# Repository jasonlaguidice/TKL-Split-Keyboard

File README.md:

# TKL-Split-Keyboard

Forked from Djinn keyboard

Board edge fillet plugin used:
https://github.com/tywtyw2002/FilletEdge

To-do list:
1. Change USB-C connector footprints to hand-solderable version (update BOM part as well)

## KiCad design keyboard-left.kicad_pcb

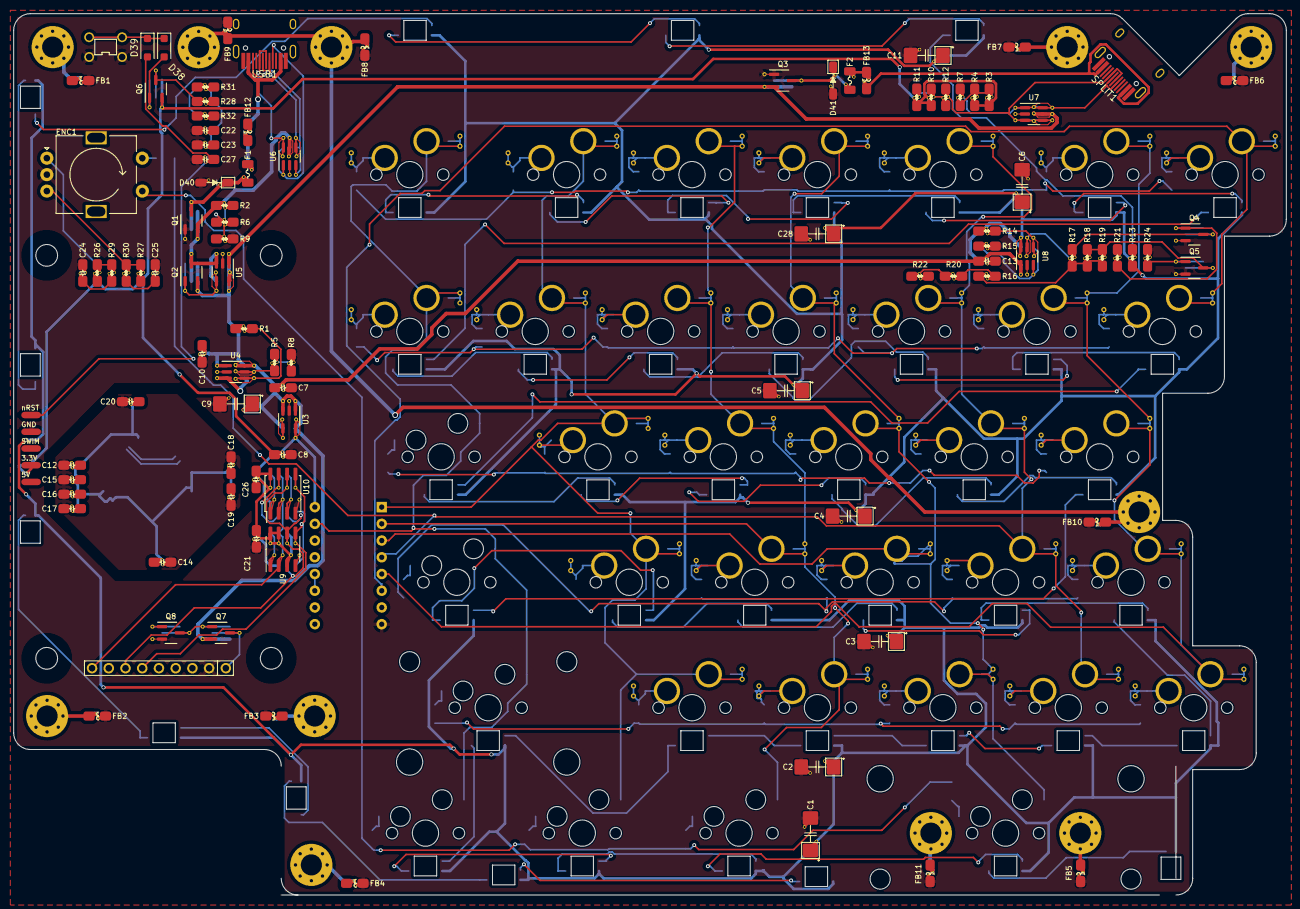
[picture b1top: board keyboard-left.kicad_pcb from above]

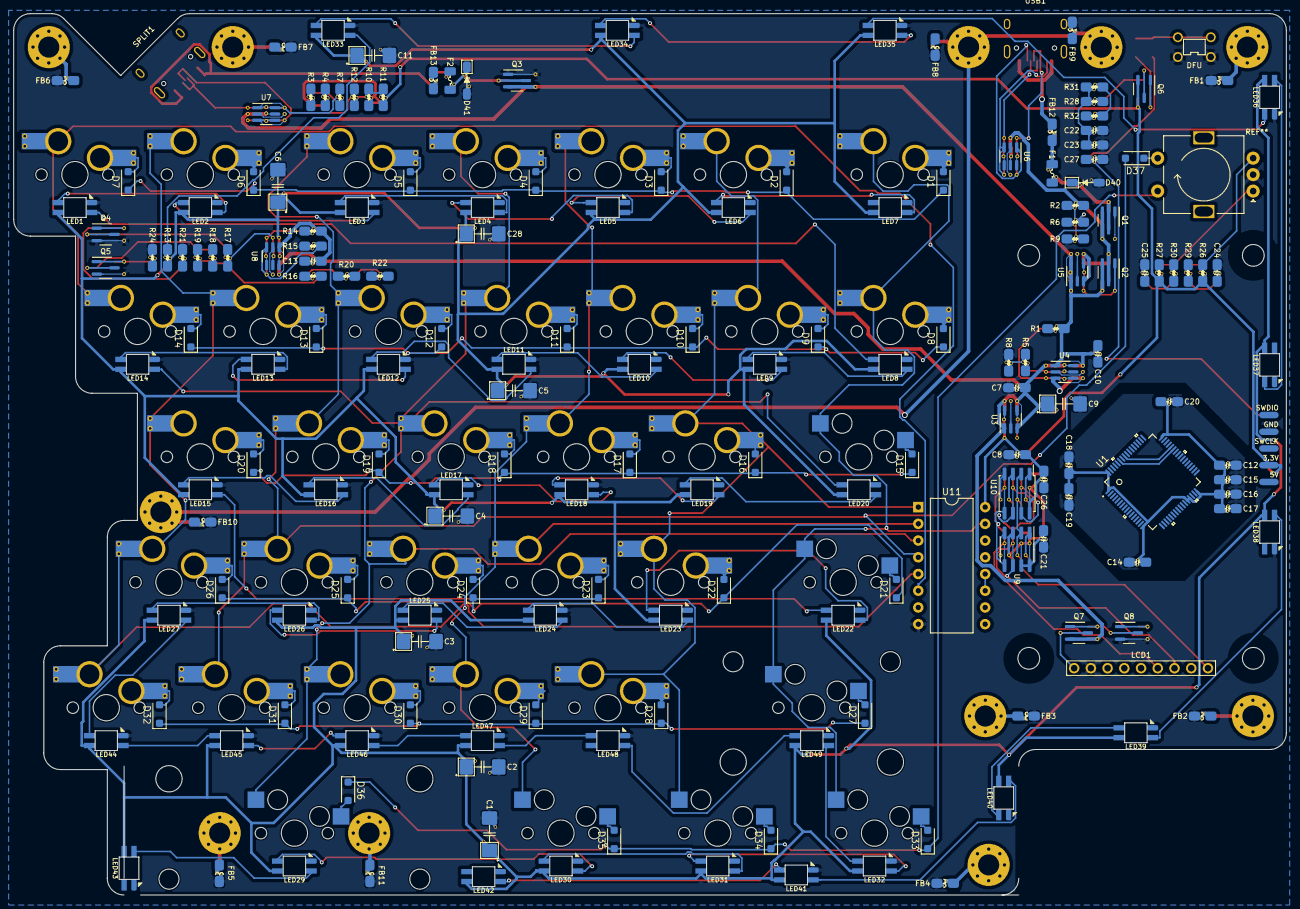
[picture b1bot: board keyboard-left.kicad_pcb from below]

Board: 2 copper layers, 193.3 x 133.9 mm, 232 parts (92 on the bottom side), 169 nets.

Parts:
C1, C2, C3, C4, C5, C6, C9, C11, C28: 100u; CP_6032
C7, C8, C10, C12: 4.7u; C-0805_2012Metric
C13, C14, C15, C16, C17, C18, C19, C20, C21, C22, C23, C24, C25, C26, C27: 100n; C-0805_2012Metric
D1, D2, D3, D4, D5, D6, D7, D8, D9, D10, D11, D12, D13, D14, D15, D16, D17, D18, D19, D20, D21, D22, D23, D24, D25, D26, D27, D28, D29, D30, D31, D32, D33, D34, D35, D36, D37, D38, D39: 1N4148; D_SOD-123F
D40, D41: SMF5.0CA; D_SOD-123
DRILL1, DRILL2, DRILL3, DRILL4, DRILL5, DRILL6, DRILL7, DRILL8, DRILL9, DRILL10, DRILL11: Drill Mountpoint; MountingHole_3.2mm_M3_Pad_Via
ENC1: Rotary_Encoder_Switch; EC11_Switch
F1: 3.0A 1206 Polyfuse; Fuse_1206_3216Metric
F2: 1.5A 1206 Polyfuse; Fuse_1206_3216Metric
FB1, FB2, FB3, FB4, FB5, FB6, FB7, FB8, FB9, FB10, FB11, FB12, FB13: 4A/0805; L-0805_2012Metric
J1: ST-Link Clone (Optional); STLink_SideSocket
LCD1: LCD-ILI9341-2.2in
LED1, LED2, LED3, LED4, LED5, LED6, LED7, LED8, LED9, LED10, LED11, LED12, LED13, LED14, LED15, LED16, LED17, LED18, LED19, LED20, LED22, LED23, LED24, LED25, LED26, LED27, LED29, LED30, LED31, LED32, LED33, LED34, LED35, LED36, LED37, LED38, LED39, LED40, LED41, LED42, LED43, LED44, LED45, LED46, LED47, LED48, LED49: SK6812 Mini-E; SK6812-MINI-E
Q1, Q2, Q3, Q7: AO3401A; SOT-23-3
Q4, Q5: 2N7002; SOT-23-3
Q6: MMUN2133LT1G; SOT-23-3
Q8: MMUN2233LT1G; SOT-23-3
R1, R3, R4, R5, R8, R10, R11, R13, R14, R15, R21, R24, R26, R27, R29, R30: 9.1k; R-0805_2012Metric
R2, R6, R9, R16, R17, R18, R19, R20, R22, R31, R32: 68k; R-0805_2012Metric
R7, R12, R28: 120; R-0805_2012Metric
RESET1: DFU; PushButton_4.5mm
SPLIT1: USB-C-2.0; HRO-TYPE-C-31-M-12-HandSoldering
SW1, SW2, SW3, SW4, SW5, SW6, SW7, SW8, SW9, SW10, SW11, SW12, SW13, SW14, SW16, SW17, SW18, SW19, SW20, SW22, SW23, SW24, SW25, SW26, SW28, SW29, SW30, SW31, SW32: SW_Push; MXOnly-1U-Hotswap-Antishear
SW15: SW_Push; MXOnly-1.5U-Hotswap
SW21: SW_Push; MXOnly-1.75U-Hotswap
SW27: SW_Push; MXOnly-2.25U-Hotswap
SW33, SW34, SW35: SW_Push; MXOnly-1.25U-Hotswap
SW36: SW_Push; MXOnly-3U-Hotswap-ReversedStabilizers
U1: STM32G474RETx
U3: AP2127K-3.3; SOT-23-5
U4, U8: TPS2553DBVR-1; SOT-23-6
U5: LMV321; SOT-23-5
U6, U7: AZC199-04S; SOT-23-6
U9: MB85RS64; SOIC-8_3.9x4.9mm_P1.27mm
U10: W25Q32JVSSIQ; SOIC-8_5.23x5.23mm_P1.27mm
U11: 74HC595; DIP-16_W10.16mm
USB1: USB-C-2.0; HRO-TYPE-C-31-M-12-HandSoldering

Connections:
+3V3: C8.1, C12.1, C14.1, C15.1, C16.1, C17.1, C18.1, C19.1, C20.1, C21.1, C26.1, J1.7, J1.8, Q6.2 (E), R3.1, R4.1, R10.1, R11.1, R26.1, R27.1, U1.1 (VBAT), U1.16 (VDD), U1.28 (VREF+), U1.29 (VDDA), U1.32 (VDD), U1.48 (VDD), U1.64 (VDD), U3.5 (VOUT), U9.3 (~W), U9.7 (~HOLD), U9.8 (VCC), U10.8 (VCC), U11.16 (VCC)
/SHIELD1: DRILL1.1, FB1.1
/SHIELD2: DRILL2.1, FB2.1
/SHIELD3: DRILL3.1, FB3.1
/SHIELD4: DRILL4.1, FB4.1
/SHIELD5: DRILL5.1, FB5.1
/SHIELD6: DRILL6.1, FB6.1
/SHIELD7: DRILL7.1, FB7.1
/SHIELD11: DRILL11.1, FB11.1
/SPLIT_COMMS_CONN+: R12.2, SPLIT1.A6 (D+), SPLIT1.B6 (D+), U7.3 (I/O4), U7.4 (I/O3)
/SPLIT_COMMS_CONN-: R7.2, SPLIT1.A7 (D-), SPLIT1.B7 (D-), U7.1 (I/O1), U7.6 (I/O2)
/VBUS_BLOCKED: Q1.2 (S), Q2.3 (D), R2.1, U5.3 (-), U6.5 (VBUS)
/VBUS_FERRITE: F1.2, FB12.1
/VBUS_FUSED: D40.1 (A1), F1.1, Q1.3 (D)
/VBUS_TRS: FB13.1, SPLIT1.A4 (VBUS), SPLIT1.B4 (VBUS)
/VBUS_TRS_FERRITE: F2.2, FB13.2
/VBUS_TRS_FUSED: D41.1 (A1), F2.1, Q3.3 (D)
BOARD_NFAULT: R1.2, U1.41 (PC9), U4.4 (~FAULT)
BOOT0: C22.2, C23.2, R28.2, R31.2, U1.61 (PB8-BOOT0)
BOOT0_CHRG: D38.2 (A), Q6.1 (B), U1.60 (PB7)
CC1: U1.43 (PA9), U1.59 (PB6), U6.3 (I/O4), USB1.B5 (CC2)
CC2: U1.44 (PA10), U1.57 (PB4), U6.1 (I/O1), USB1.A5 (CC1)
COL1: SW1.2, SW8.2, SW15.2, SW21.2, SW27.2, SW33.2, U11.15 (QA)
COL2: SW2.2, SW9.2, SW16.2, SW22.2, SW28.2, SW34.2, U11.1 (QB)
COL3: SW3.2, SW10.2, SW17.2, SW23.2, SW29.2, SW35.2, U11.2 (QC)
COL4: SW4.2, SW11.2, SW18.2, SW24.2, SW30.2, SW36.2, U11.3 (QD)
COL5: D37.2 (A), SW5.2, SW12.2, SW19.2, SW25.2, SW31.2, U11.4 (QE)
COL6: SW6.2, SW13.2, SW20.2, SW26.2, SW32.2, U11.5 (QF)
COL7: SW7.2, SW14.2, U11.6 (QG)
CURR_1500mA_OK: Q4.1 (G), R21.1, U1.23 (PC5)
CURR_3000mA_OK: Q5.1 (G), R24.1, U1.22 (PC4)
CURR_LIM: R16.1, R17.1, R18.1, R19.1, U8.5 (ILIM)
D+: U1.46 (PA12), U6.6 (I/O2), USB1.A6 (D+), USB1.B6 (D+)
D-: U1.45 (PA11), U6.4 (I/O3), USB1.A7 (D-), USB1.B7 (D-)
EEP_CS: U1.58 (PB5), U9.1 (~S)
ENC_A: C24.1, R29.1, U1.3 (PC14-OSC32_IN)
ENC_B: C25.1, R30.1, U1.4 (PC15-OSC32_OUT)
FLASH_CS: U1.42 (PA8), U10.1 (~CS)
GND: C1.2, C2.2, C3.2, C4.2, C5.2, C6.2, C7.2, C8.2, C9.2, C10.2, C11.2, C12.2, C13.2, C14.2, C15.2, C16.2, C17.2, C18.2, C19.2, C20.2, C21.2, C22.1, C23.1, C24.2, C25.2, C26.2, C27.1, C28.2, D40.2 (A2), D41.2 (A2), ENC1.C, FB1.2, FB2.2, FB3.2, FB4.2, FB5.2, FB6.2, FB7.2, FB8.2, FB9.2, FB10.2, FB11.2, J1.3, J1.4, LCD1.8, LED1.3 (GND), LED2.3 (GND), LED3.3 (GND), LED4.3 (GND), LED5.3 (GND), LED6.3 (GND), LED7.3 (GND), LED8.3 (GND), LED9.3 (GND), LED10.3 (GND), LED11.3 (GND), LED12.3 (GND), LED13.3 (GND), LED14.3 (GND), LED15.3 (GND), LED16.3 (GND), LED17.3 (GND), LED18.3 (GND), LED19.3 (GND), LED20.3 (GND), LED22.3 (GND), LED23.3 (GND), LED24.3 (GND), LED25.3 (GND), LED26.3 (GND), LED27.3 (GND), LED29.3 (GND), LED30.3 (GND), LED31.3 (GND), LED32.3 (GND), LED33.3 (GND), LED34.3 (GND), LED35.3 (GND), LED36.3 (GND), LED37.3 (GND), LED38.3 (GND), LED39.3 (GND), LED40.3 (GND), LED41.3 (GND), LED42.3 (GND), LED43.3 (GND), LED44.3 (GND), LED45.3 (GND), LED46.3 (GND), LED47.3 (GND), LED48.3 (GND), LED49.3 (GND), Q1.1 (G), Q3.1 (G), Q4.2 (S), Q5.2 (S), Q8.2 (E), R8.2, R9.2, R15.2, R21.2, R22.2, R24.2, R32.2, RESET1.1, SPLIT1.A1 (GND), SPLIT1.B1 (GND), U1.15 (VSS), U1.27 (VSSA), U1.31 (VSS), U1.47 (VSS), U1.63 (VSS), U3.2 (GND), U4.2 (GND), U5.2 (V-), U6.2 (GND), U7.2 (GND), U8.2 (GND), U9.4 (VSS), U10.4 (GND), U11.8 (GND), USB1.A1 (GND), USB1.B1 (GND)
LCD_BL_PWM: LCD1.2, U1.21 (PA7)
LCD_CS: LCD1.7, U1.55 (PD2)
LCD_DC: LCD1.5, U1.51 (PA15)
LCD_EN: Q8.1 (B), U1.20 (PA6)
LCD_PWR: LCD1.9, Q7.3 (D)
LCD_RST: LCD1.6, U1.56 (PB3)
MISO: LCD1.1, U1.53 (PC11), U9.2 (Q), U10.2 (DO(IO1))
MOSI: LCD1.4, U1.54 (PC12), U9.5 (D), U10.5 (DI(IO0))
MTX_CLK: U1.8 (PC0), U11.11 (SRCLK), U11.12 (RCLK)
MTX_OE: U1.9 (PC1), U11.13 (~OE)
MTX_SERIAL: U1.10 (PC2), U11.14 (SER)
MTX_SRCLR: U1.11 (PC3), U11.10 (~SRCLR)
NRST: C27.2, D39.2 (A), J1.1, U1.7 (PG10-NRST)
unnamed: D1.2 (A), SW1.1
unnamed: D2.2 (A), SW2.1
unnamed: D3.2 (A), SW3.1
unnamed: D4.2 (A), SW4.1
unnamed: D5.2 (A), SW5.1
unnamed: D6.2 (A), SW6.1
unnamed: D7.2 (A), SW7.1
unnamed: D8.2 (A), SW8.1
unnamed: D9.2 (A), SW9.1
unnamed: D10.2 (A), SW10.1
unnamed: D11.2 (A), SW11.1
unnamed: D12.2 (A), SW12.1
unnamed: D13.2 (A), SW13.1
unnamed: D14.2 (A), SW14.1
unnamed: D15.2 (A), SW15.1
unnamed: D16.2 (A), SW16.1
unnamed: D17.2 (A), SW17.1
unnamed: D18.2 (A), SW18.1
unnamed: D19.2 (A), SW19.1
unnamed: D20.2 (A), SW20.1
unnamed: D21.2 (A), SW21.1
unnamed: D22.2 (A), SW22.1
unnamed: D23.2 (A), SW23.1
unnamed: D24.2 (A), SW24.1
unnamed: D25.2 (A), SW25.1
unnamed: D26.2 (A), SW26.1
unnamed: D27.2 (A), SW27.1
unnamed: D28.2 (A), SW28.1
unnamed: D29.2 (A), SW29.1
unnamed: D30.2 (A), SW30.1
unnamed: D31.2 (A), SW31.1
unnamed: D32.2 (A), SW32.1
unnamed: D33.2 (A), SW33.1
unnamed: D34.2 (A), SW34.1
unnamed: D35.2 (A), SW35.1
unnamed: D36.2 (A), SW36.1
unnamed: D37.1 (K), ENC1.S2
unnamed: D38.1 (K), D39.1 (K), RESET1.2
unnamed: LED1.4 (DIN), LED8.2 (DOUT)
unnamed: LED1.2 (DOUT), LED2.4 (DIN)
unnamed: LED2.2 (DOUT), LED3.4 (DIN)
unnamed: LED3.2 (DOUT), LED4.4 (DIN)
unnamed: LED4.2 (DOUT), LED5.4 (DIN)
unnamed: LED5.2 (DOUT), LED6.4 (DIN)
unnamed: LED6.2 (DOUT), LED7.4 (DIN)
unnamed: LED8.4 (DIN), LED9.2 (DOUT)
unnamed: LED10.4 (DIN), LED11.2 (DOUT)
unnamed: LED9.4 (DIN), LED10.2 (DOUT)
unnamed: LED11.4 (DIN), LED12.2 (DOUT)
unnamed: LED12.4 (DIN), LED13.2 (DOUT)
unnamed: LED13.4 (DIN), LED14.2 (DOUT)
unnamed: LED14.4 (DIN), LED20.2 (DOUT)
unnamed: LED15.4 (DIN), LED22.2 (DOUT)
unnamed: LED15.2 (DOUT), LED16.4 (DIN)
unnamed: LED16.2 (DOUT), LED17.4 (DIN)
unnamed: LED17.2 (DOUT), LED18.4 (DIN)
unnamed: LED18.2 (DOUT), LED19.4 (DIN)
unnamed: LED19.2 (DOUT), LED20.4 (DIN)
unnamed: LED22.4 (DIN), LED23.2 (DOUT)
unnamed: LED23.4 (DIN), LED24.2 (DOUT)
unnamed: LED24.4 (DIN), LED25.2 (DOUT)
unnamed: LED25.4 (DIN), LED26.2 (DOUT)
unnamed: LED26.4 (DIN), LED27.2 (DOUT)
unnamed: LED27.4 (DIN), LED44.2 (DOUT)
unnamed: LED29.2 (DOUT), LED30.4 (DIN)
unnamed: LED30.2 (DOUT), LED31.4 (DIN)
unnamed: LED31.2 (DOUT), LED32.4 (DIN)
unnamed: LED32.2 (DOUT), LED49.4 (DIN)
unnamed: LED33.2 (DOUT), LED34.4 (DIN)
unnamed: LED34.2 (DOUT), LED35.4 (DIN)
unnamed: LED35.2 (DOUT), LED36.4 (DIN)
unnamed: LED36.2 (DOUT), LED37.4 (DIN)
unnamed: LED37.2 (DOUT), LED38.4 (DIN)
unnamed: LED38.2 (DOUT), LED39.4 (DIN)
unnamed: LED39.2 (DOUT), LED40.4 (DIN)
unnamed: LED40.2 (DOUT), LED41.4 (DIN)
unnamed: LED41.2 (DOUT), LED42.4 (DIN)
unnamed: LED42.2 (DOUT), LED43.4 (DIN)
unnamed: LED44.4 (DIN), LED45.2 (DOUT)
unnamed: LED45.4 (DIN), LED46.2 (DOUT)
unnamed: LED46.4 (DIN), LED47.2 (DOUT)
unnamed: LED47.4 (DIN), LED48.2 (DOUT)
unnamed: LED48.4 (DIN), LED49.2 (DOUT)
unnamed: Q2.1 (G), U5.4
unnamed: Q4.3 (D), R17.2
unnamed: Q5.3 (D), R18.2, R19.2
unnamed: Q6.3 (C), R28.1
unnamed: Q7.1 (G), Q8.3 (C)
unnamed: R5.2, R8.1
unnamed: R6.2, R9.1
unnamed: R16.2, R20.2
unnamed: R20.1, R22.1
unnamed: R31.1, R32.1
unnamed: R5.1, U4.5 (ILIM)
PLUG_DETECT: R2.2, R6.1, U1.34 (PB12)
ROT_A: ENC1.A, R26.2, R29.2
ROT_B: ENC1.B, R27.2, R30.2
ROW1: D1.1 (K), D2.1 (K), D3.1 (K), D4.1 (K), D5.1 (K), D6.1 (K), D7.1 (K), U1.35 (PB13)
ROW2: D8.1 (K), D9.1 (K), D10.1 (K), D11.1 (K), D12.1 (K), D13.1 (K), D14.1 (K), U1.36 (PB14)
ROW3: D15.1 (K), D16.1 (K), D17.1 (K), D18.1 (K), D19.1 (K), D20.1 (K), U1.37 (PB15)
ROW4: D21.1 (K), D22.1 (K), D23.1 (K), D24.1 (K), D25.1 (K), D26.1 (K), U1.38 (PC6)
ROW5: D27.1 (K), D28.1 (K), D29.1 (K), D30.1 (K), D31.1 (K), D32.1 (K), U1.39 (PC7)
ROW6: D33.1 (K), D34.1 (K), D35.1 (K), D36.1 (K), ENC1.S1, U1.40 (PC8)
SCK: LCD1.3, U1.52 (PC10), U9.6 (C), U10.6 (CLK)
SHIELD: DRILL8.1, DRILL9.1, DRILL10.1, FB8.1, FB9.1, FB10.1
SK6812_EN: R15.1, U1.24 (PB0), U8.3 (EN)
SK6812_MTRX_IN: LED29.4 (DIN), LED43.2 (DOUT)
SK6812_NFAULT: R14.2, U1.25 (PB1), U8.4 (~FAULT)
SK6812_PWM: LED33.4 (DIN), R13.2, U1.26 (PB2)
SK6812_PWR: C1.1, C2.1, C3.1, C4.1, C5.1, C6.1, C11.1, C28.1, LED1.1 (VDD), LED2.1 (VDD), LED3.1 (VDD), LED4.1 (VDD), LED5.1 (VDD), LED6.1 (VDD), LED7.1 (VDD), LED8.1 (VDD), LED9.1 (VDD), LED10.1 (VDD), LED11.1 (VDD), LED12.1 (VDD), LED13.1 (VDD), LED14.1 (VDD), LED15.1 (VDD), LED16.1 (VDD), LED17.1 (VDD), LED18.1 (VDD), LED19.1 (VDD), LED20.1 (VDD), LED22.1 (VDD), LED23.1 (VDD), LED24.1 (VDD), LED25.1 (VDD), LED26.1 (VDD), LED27.1 (VDD), LED29.1 (VDD), LED30.1 (VDD), LED31.1 (VDD), LED32.1 (VDD), LED33.1 (VDD), LED34.1 (VDD), LED35.1 (VDD), LED36.1 (VDD), LED37.1 (VDD), LED38.1 (VDD), LED39.1 (VDD), LED40.1 (VDD), LED41.1 (VDD), LED42.1 (VDD), LED43.1 (VDD), LED44.1 (VDD), LED45.1 (VDD), LED46.1 (VDD), LED47.1 (VDD), LED48.1 (VDD), LED49.1 (VDD), R13.1, U8.6 (OUT)
SPLIT_COMMS+: R10.2, R11.2, R12.1, U1.33 (PB11)
SPLIT_COMMS-: R3.2, R4.2, R7.1, U1.30 (PB10)
SWCLK: J1.6, U1.50 (PA14)
SWDIO: J1.2, U1.49 (PA13)
VBUS: C10.1, Q2.2 (S), Q3.2 (S), R1.1, U4.1 (IN), U4.3 (EN), U5.1 (+), U5.5 (V+), U7.5 (VBUS)
VDD: C7.1, C9.1, C13.1, Q7.2 (S), R14.1, U3.1 (VIN), U3.3 (EN), U4.6 (OUT), U8.1 (IN)
V_USB: FB12.2, USB1.A4 (VBUS), USB1.B4 (VBUS)

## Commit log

2023-06-26 Closeout changes
2023-06-26 Cleanup extra files
2023-06-26 Ignore .vscode folder
2023-06-26 Correct .gitignore
2023-06-26 CQ tinkering
2023-06-28 Started placing MCU support group
2023-06-29 Start with USB support
2023-06-30 Minor progress on component grouping
2023-07-05 More component groupings
2023-07-06 Board layout drawings added
2023-07-10 LED Flips
2023-07-11 Added a single corner radius
2023-07-13 Final component placements
2023-07-13 Auto routing
2023-07-17 Initial routing for price
2023-07-18 Gerber file generation
2023-07-19 Fillet board edges @ 2.54mm
2023-08-02 Pre-repositioning MCU
